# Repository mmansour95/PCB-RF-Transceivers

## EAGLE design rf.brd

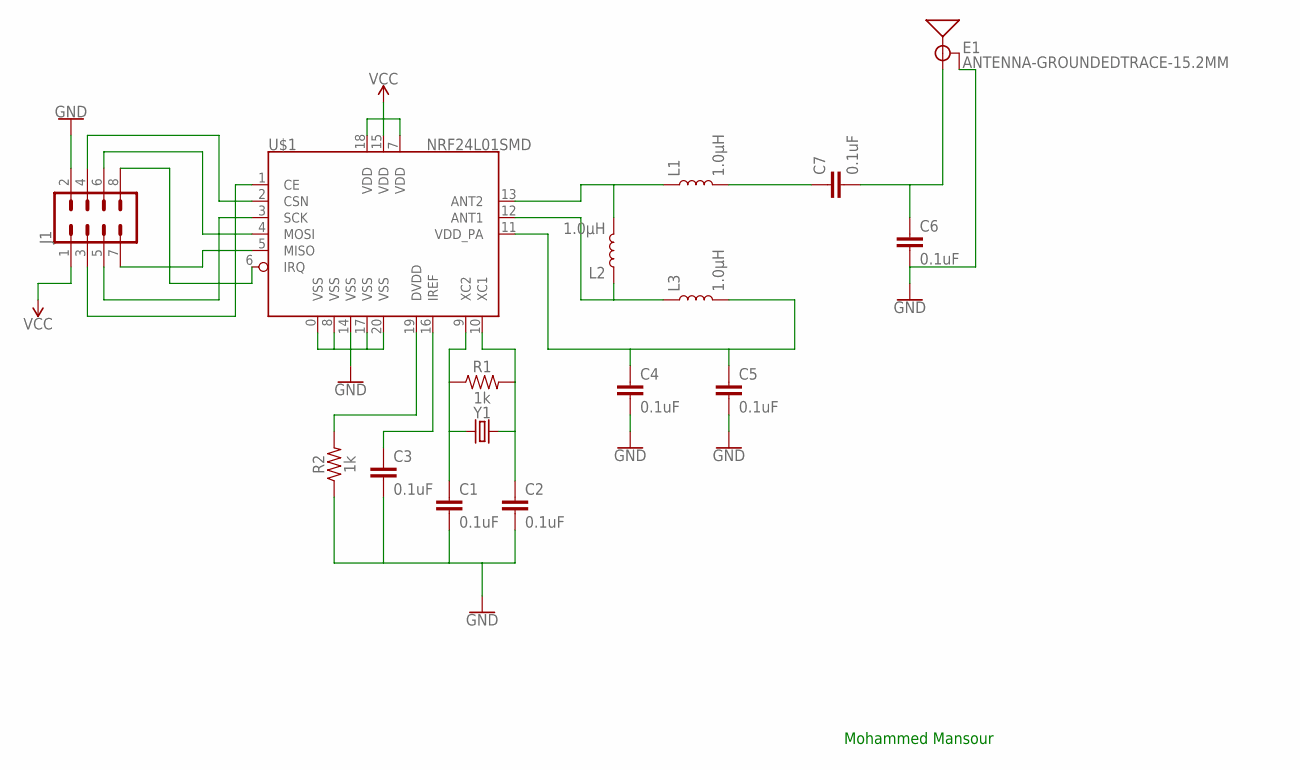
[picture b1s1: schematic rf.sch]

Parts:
C1, C2, C3, C4, C5, C6, C7: 0.1uF; 0402-TIGHT
E1: ANTENNA-GROUNDEDTRACE-15.2MM; TRACE_ANTENNA_2.4GHZ_15.2MM
J1: CONN_04X2; 2X4
L1, L2, L3: 1.0μH; 0805-WIDE
R1, R2: 1k; 0402-TIGHT
U$1: NRF24L01SMD; QFN20-4X4MM
Y1: CRYSTALSMD-3.2X1.5; CRYSTAL-SMD-3.2X1.5MM

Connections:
GND: C1.2, C2.2, C3.2, C4.2, C5.2, C6.2, E1.GND, J1.2, R2.1, U$1.0 (VSS), U$1.8 (VSS), U$1.14 (VSS), U$1.17 (VSS), U$1.20 (VSS)
unnamed: J1.3, U$1.1 (CE)
unnamed: J1.4, U$1.2 (CSN)
unnamed: C1.1, R1.1, U$1.9 (XC2), Y1.P$1 (1)
unnamed: C2.1, R1.2, U$1.10 (XC1), Y1.P$2 (2)
unnamed: J1.5, U$1.3 (SCK)
unnamed: R2.2, U$1.19 (DVDD)
unnamed: C3.1, U$1.16 (IREF)
unnamed: J1.6, U$1.4 (MOSI)
unnamed: J1.7, U$1.5 (MISO)
unnamed: L1.1, L2.2, U$1.13 (ANT2)
unnamed: C7.1, L1.2
unnamed: C6.1, C7.2, E1.ANT (SIGNAL)
unnamed: C4.1, C5.1, L3.2, U$1.11 (VDD_PA)
unnamed: J1.8, U$1.6 (IRQ)
unnamed: L2.1, L3.1, U$1.12 (ANT1)
VCC: J1.1, U$1.7 (VDD), U$1.15 (VDD), U$1.18 (VDD)

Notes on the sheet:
Mohammed Mansour

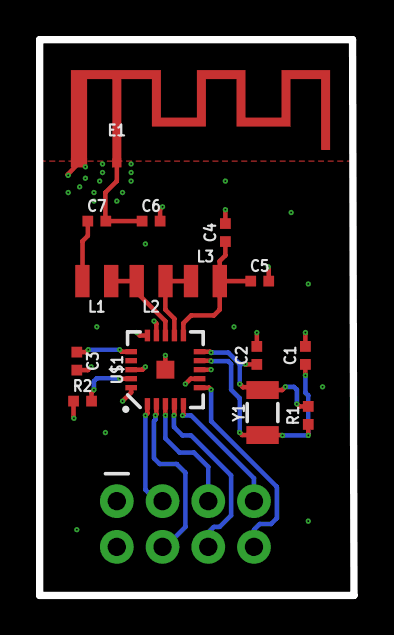
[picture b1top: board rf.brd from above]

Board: 4 copper layers, 17.5 x 30.9 mm, 16 parts (1 on the bottom side), 17 nets.

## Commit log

2021-05-10 my project

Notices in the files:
parts and their libraries:
SparkFun-Capacitors: Licensing: Creative Commons ShareAlike 4.0 International - https://creativecommons.org/licenses/by-sa/4.0
